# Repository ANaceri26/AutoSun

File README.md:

# AutoSun: Solar RC Car Board

One circuit board that runs a small solar-powered RC car. It charges the batteries from solar panels, swaps between two battery packs on its own, drives two rear motors and a steering servo, and holds an Arduino Nano Every as the brain.

## What the board does
- **Solar charging:** 4 small panels, wired as two pairs, charge the batteries, getting as much power from the sun as they can.
- **Two battery packs:** one drives the car while the other charges. The board switches between them automatically.
- **5 V supply:** powers the Arduino, the servo and the sensors. It stays on during a battery swap, so the Arduino never restarts.
- **Motor driver:** runs the left and right rear motors, with a built-in current limit so they can't be overloaded.
- **Plug-in spots:** steering servo, ultrasonic distance sensor, IR remote receiver, and a spare I2C port.
- **Phone control (Wi-Fi):** a spot for a XIAO ESP32-S3, with a built-in 3.3 V ↔ 5 V level shifter, so a phone can drive the car and show live battery and solar data. See `docs/phone_dashboard_plan.md`.
- **Plugs:** JST-PH 2.0 for the solar panels, both battery packs and both motors.

## Folders
| Where | What's in it |
|---|---|
| `solar_car.kicad_pro` | The KiCad 10 project. Open this to see the circuit and the board. |
| `builds/A_full_assembly/` | **Version A, ready to order:** the factory builds and solders everything except the Arduino and pin headers. Upload `gerbers_upload_this.zip`, `BOM_JLCPCB.csv` and `CPL_JLCPCB.csv`. |
| `builds/B_own_modules/` | **Version B (dropped, kept for reference only):** same board, but it uses my own red DRV8833 motor module and MP1584 5 V module instead of factory-soldered chips. Cheaper, with a bit more soldering. Same 3 files to upload. Its KiCad project is in `kicad/`. |
| `mechanical/` | For the car body: 3D models (STEP) and AutoCAD drawings (DXF), plus a sheet with every size, hole position and height. |
| `docs/` | The phone dashboard plan, and **first power-up steps** (follow these when the board arrives). |
| `sim/` | Tests: LTspice simulations (battery swap, level shifter, XIAO power) and a voltage/current stress check of the whole board. All pass. |
| `schematic_preview.png` | A quick picture of the circuit. |

The build folder has `YOU_SOLDER_THESE.csv` listing what you solder yourself: the Arduino, the XIAO and the pin headers.

## Board legend
Every plug, what goes in it, and which pin is +: see `board_legend.png` in each build folder.

## Winter charging (USB-C, no sun)
No board change needed. You make a small adapter cable instead of using the solar panels:

1. Get a **USB-C PD trigger board that outputs a fixed 12 V** (a few dollars). Fixed 12 V boards can't be set wrong. On adjustable ones, 5 V or 9 V just won't charge (simulated in `sim/charging_inputs.cir`).
2. Solder its output to a female JST-PH cable: **red to +, black to −**.
3. Unplug the solar panels from **J1** and plug the adapter in. On J1, the **left pin is +**.
4. Plug a USB-C power bank or wall charger into the trigger board. It must support USB-C PD at **12 V** (look for "12V" in its output specs; some only do 5 V and 9 V).
5. **Switch the car ON** with the main switch. The Arduino decides which pack charges, so nothing charges while it's off.

The charger then runs at its full rate (about 1 A), so a drained pack fills in about 2–3 hours. If + and − are swapped by mistake, the input diode blocks it: nothing breaks, it just won't charge.

## Open it
Install [KiCad 10](https://www.kicad.org/), then open `solar_car.kicad_pro`. In the board view, press `Alt+3` for 3D.

## Status
The board is fully laid out, passes KiCad's design checks, and every part has a JLCPCB part number. **Not ordered yet.**

Next up: write the Arduino code (driving, battery swap, IR remote, and self-driving with the ultrasonic sensor).

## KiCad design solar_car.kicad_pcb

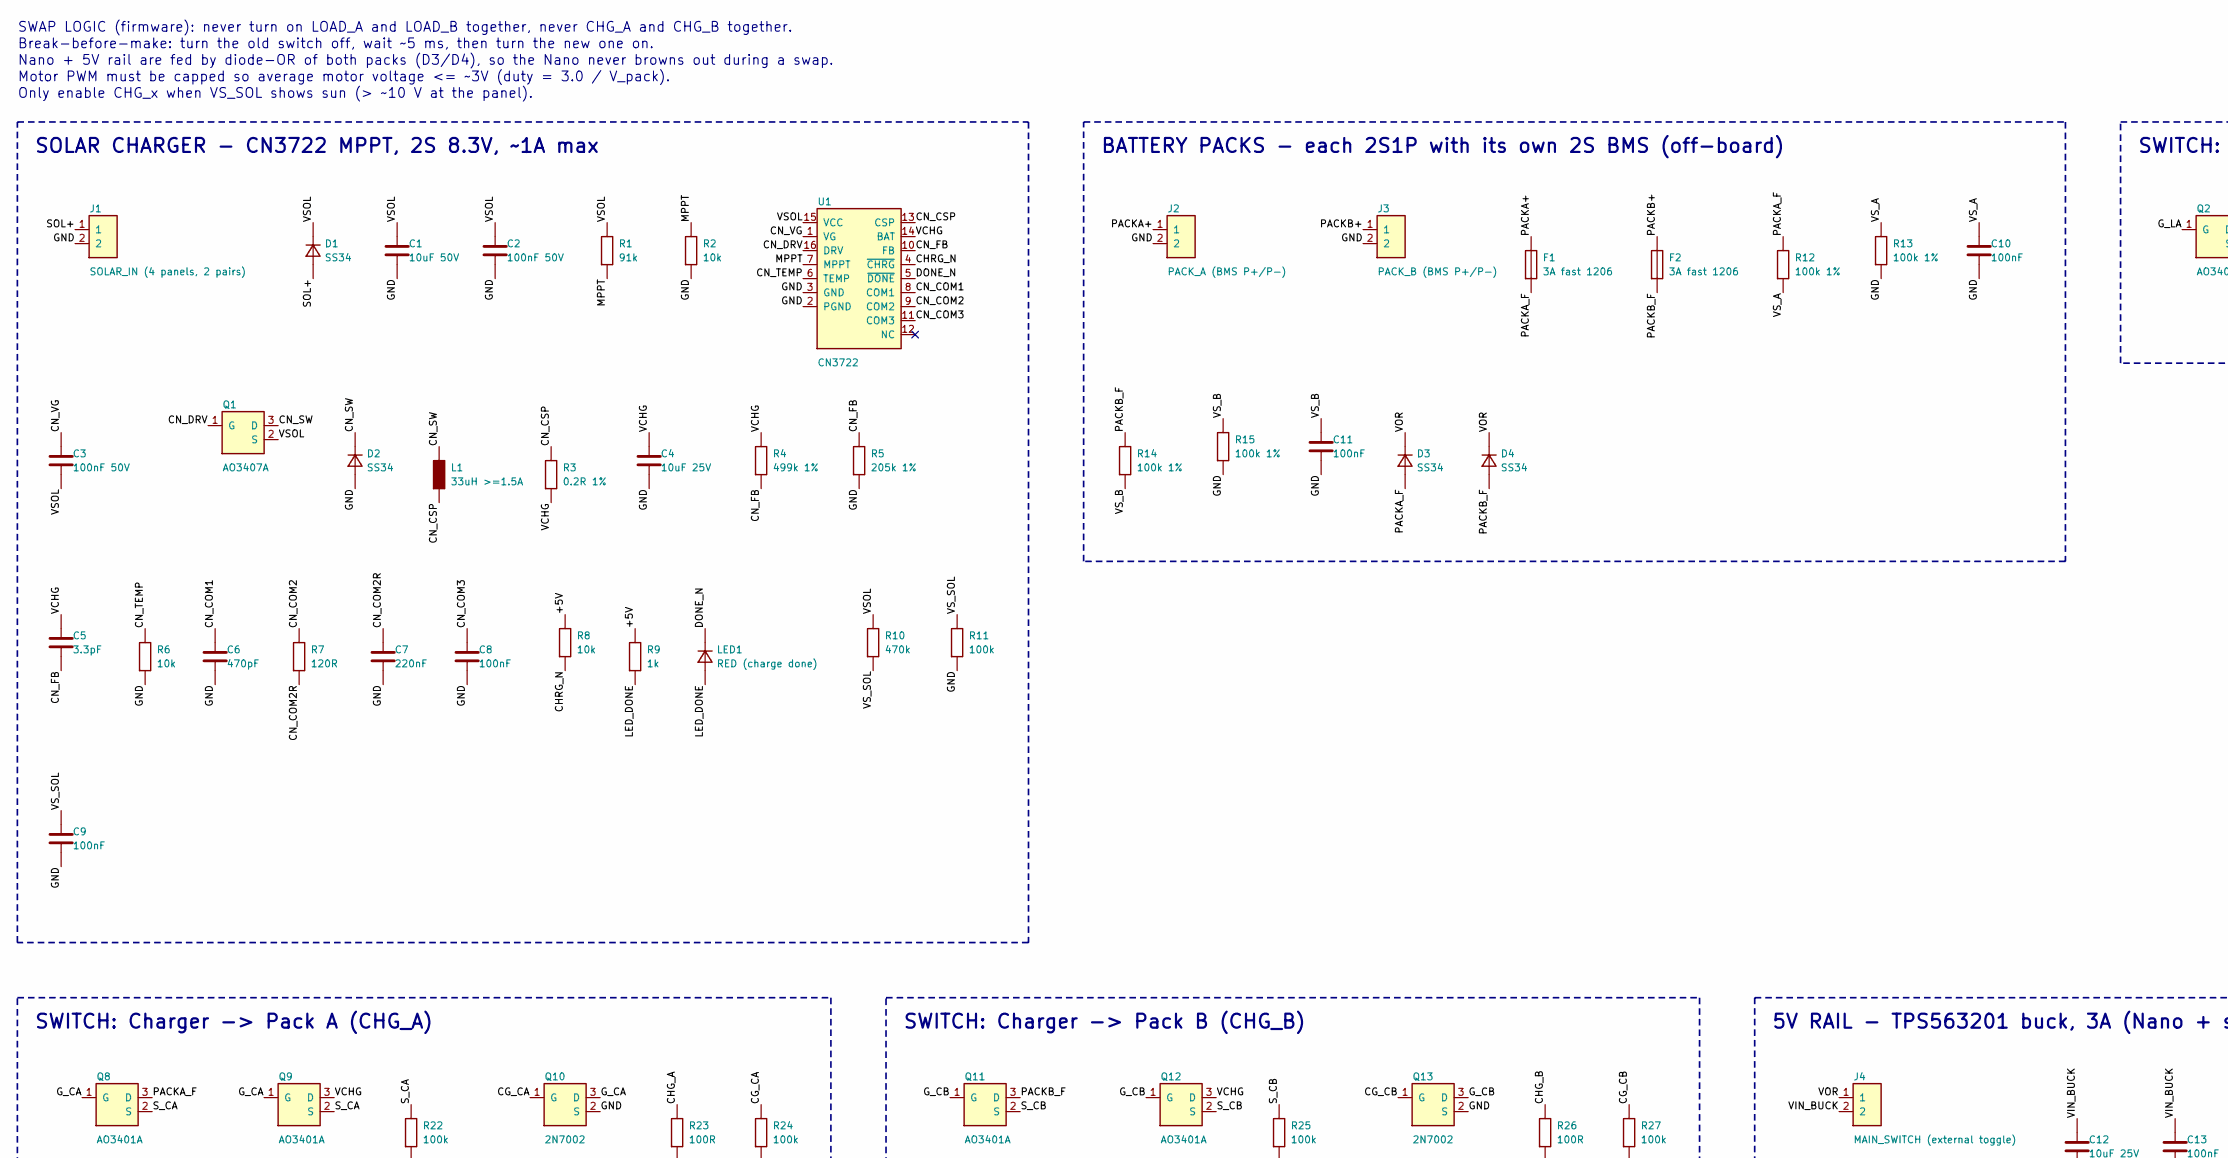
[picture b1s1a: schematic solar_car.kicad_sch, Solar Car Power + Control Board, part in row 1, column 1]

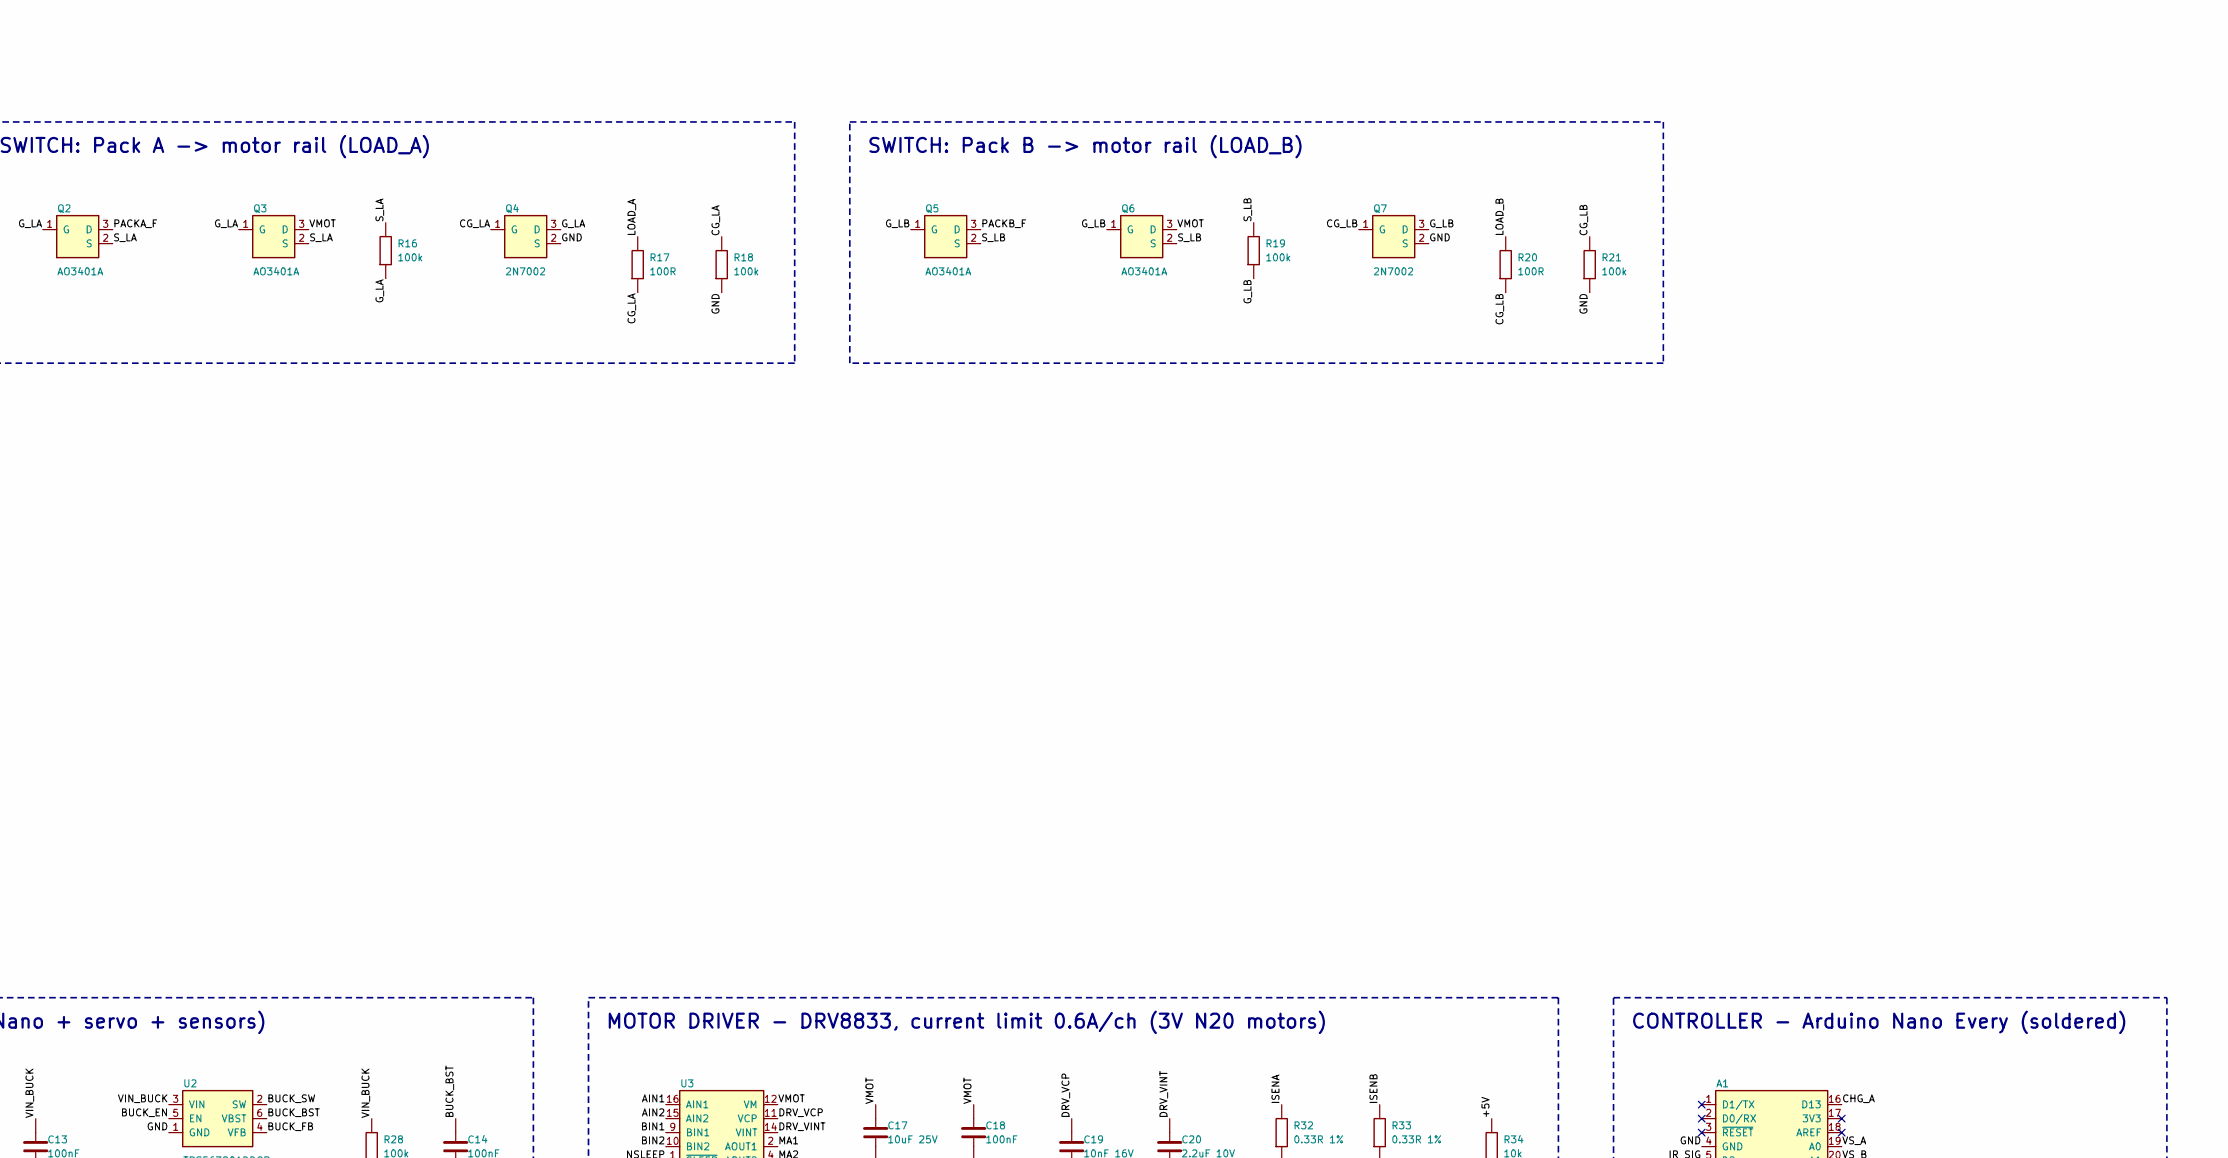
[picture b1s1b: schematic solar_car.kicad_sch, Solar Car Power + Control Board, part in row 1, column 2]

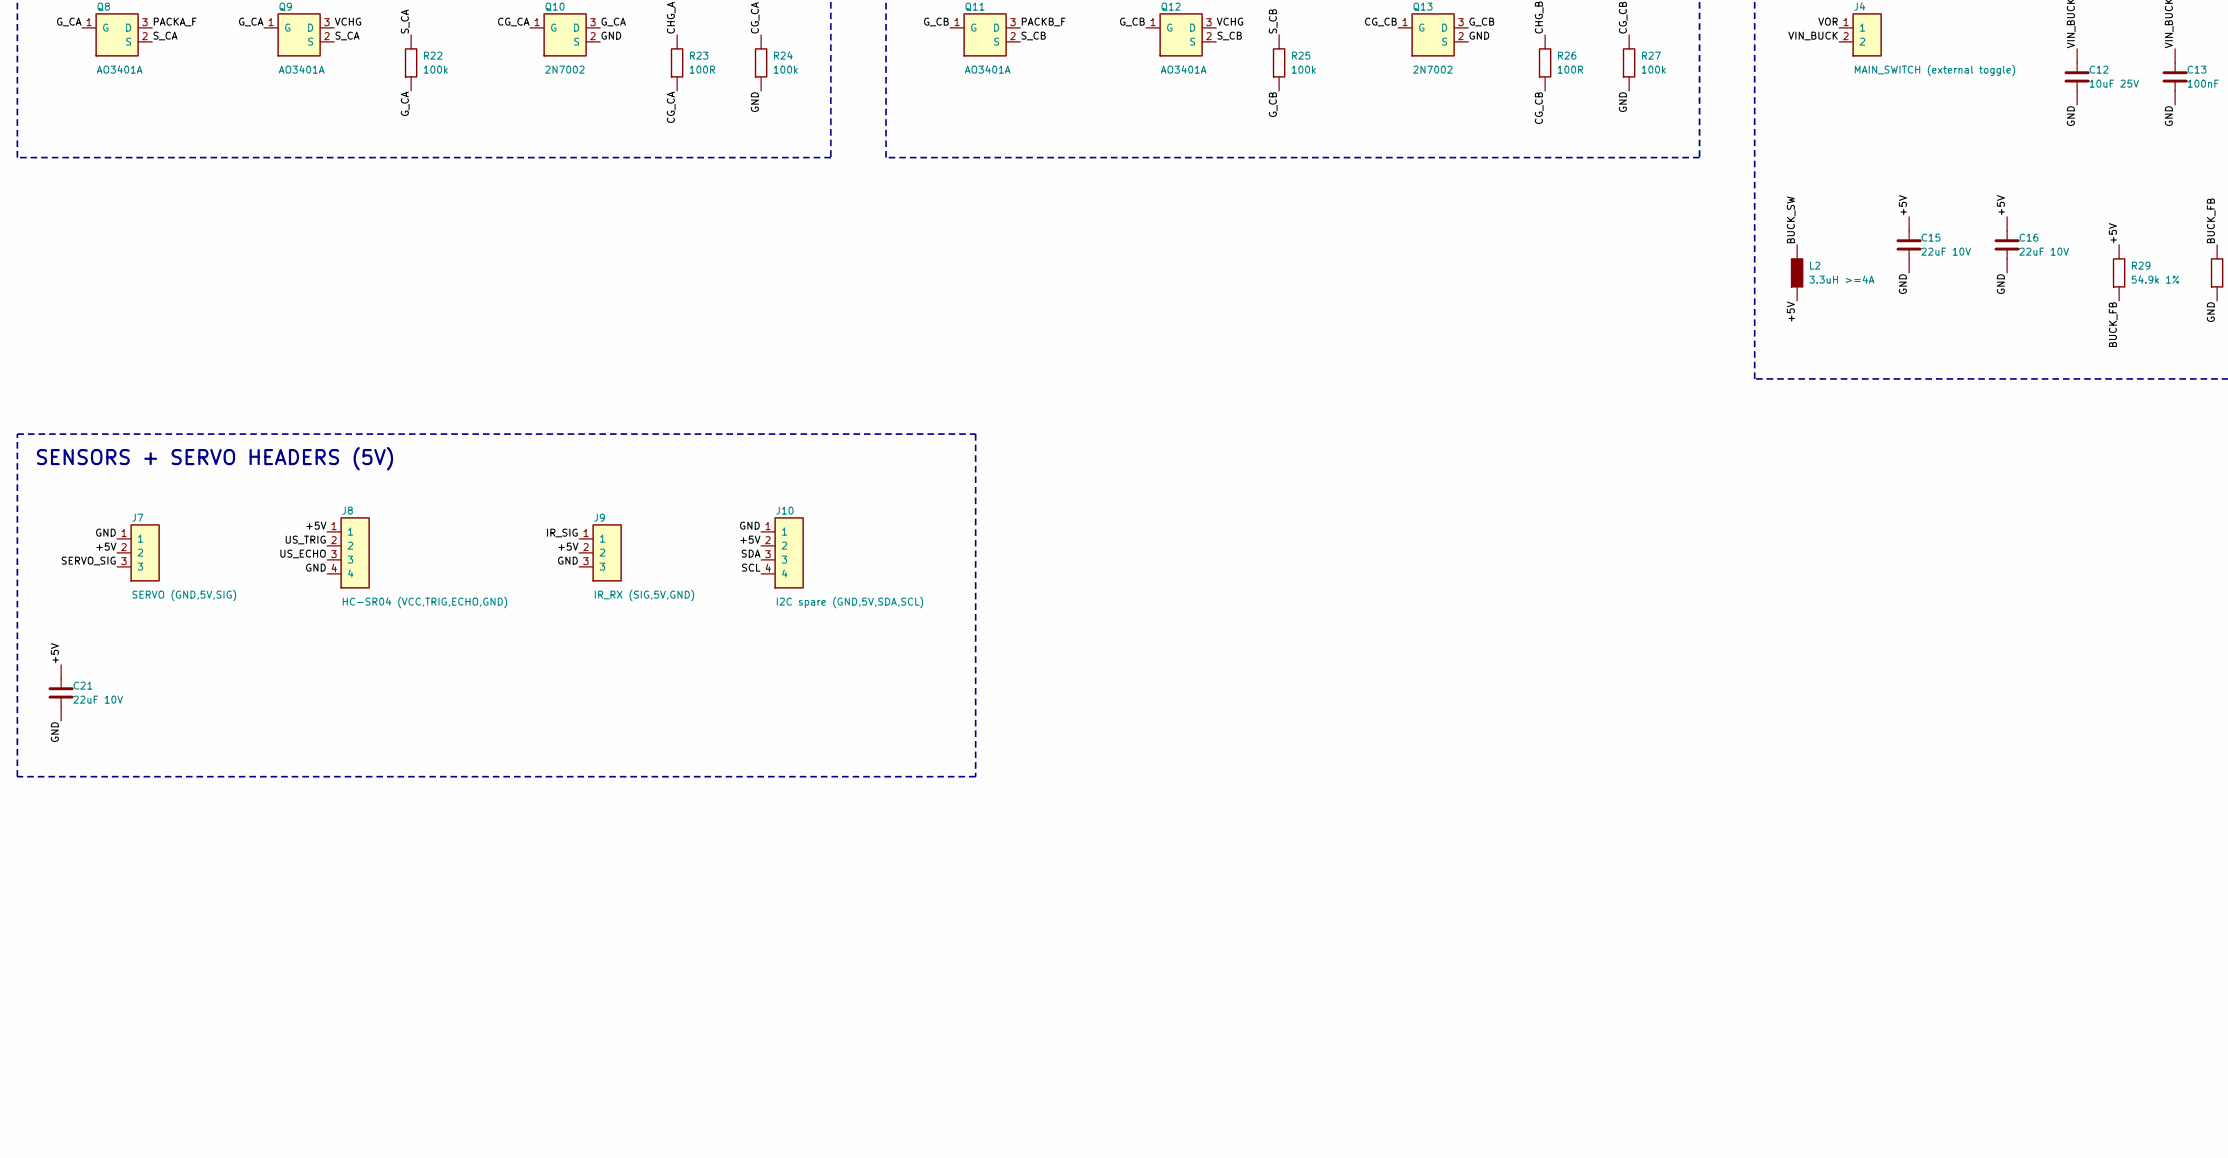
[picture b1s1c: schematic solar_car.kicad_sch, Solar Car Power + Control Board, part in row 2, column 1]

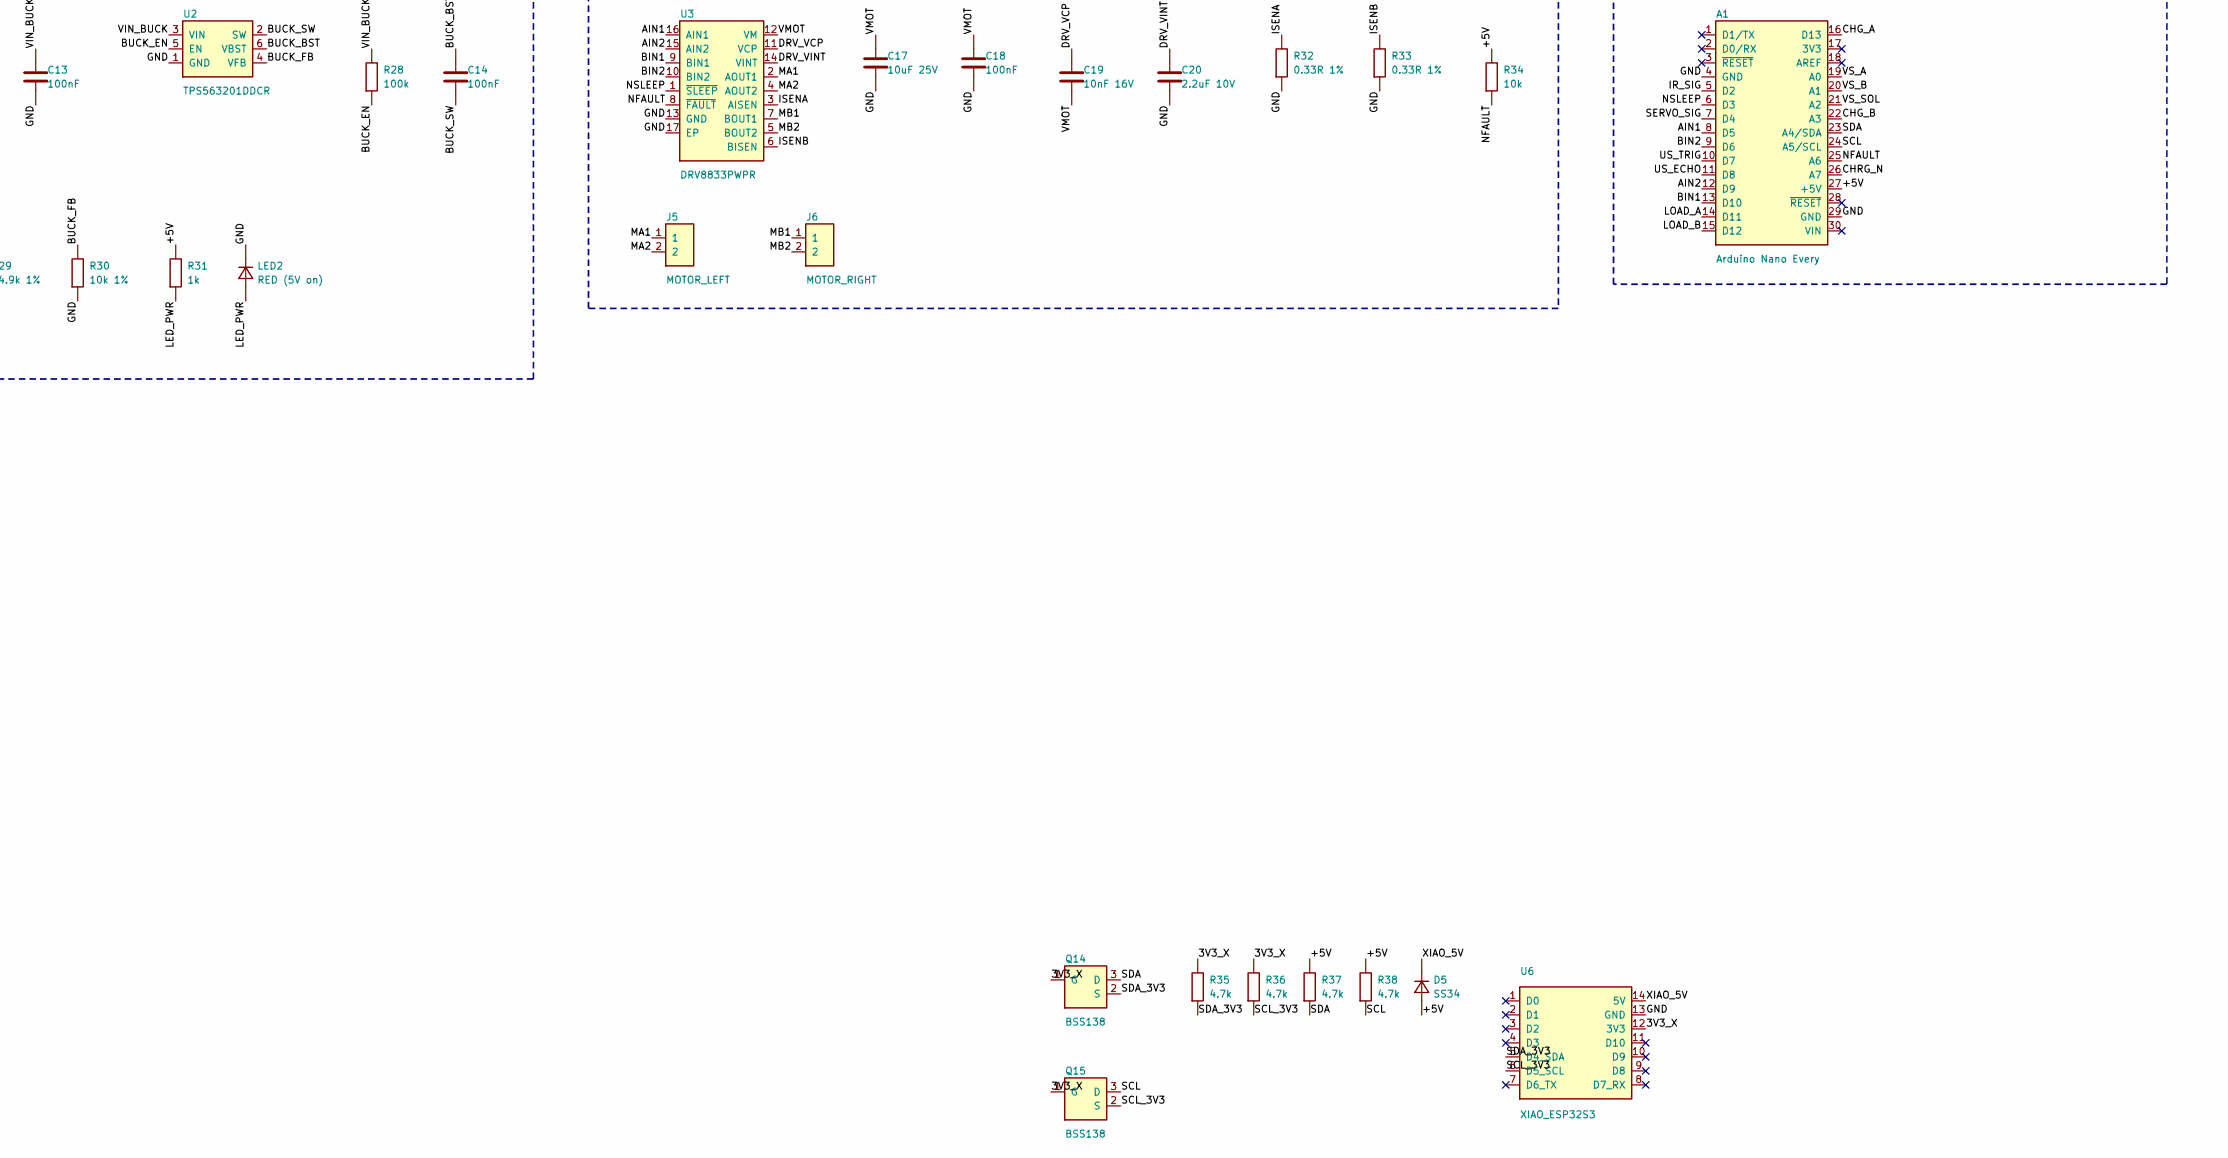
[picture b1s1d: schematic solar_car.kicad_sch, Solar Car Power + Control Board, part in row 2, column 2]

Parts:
A1: Arduino Nano Every; Arduino_Nano; MPN ABX00028
C1: 10uF 50V; C_1206_3216Metric; LCSC C13585
C2, C3: 100nF 50V; C_0603_1608Metric; LCSC C14663
C4, C12, C17: 10uF 25V; C_1206_3216Metric; LCSC C13585
C5: 3.3pF; C_0603_1608Metric; LCSC C1660
C6: 470pF; C_0603_1608Metric; LCSC C1620
C7: 220nF; C_0603_1608Metric; LCSC C21120
C8, C9, C10, C11, C13, C14, C18: 100nF; C_0603_1608Metric; LCSC C14663
C15, C16, C21: 22uF 10V; C_1206_3216Metric; LCSC C12891
C19: 10nF 16V; C_0603_1608Metric; LCSC C57112
C20: 2.2uF 10V; C_0603_1608Metric; LCSC C23630
D1, D2, D3, D4, D5: SS34; D_SMA; MPN SS34; LCSC C8678
F1, F2: 3A fast 1206; Fuse_1206_3216Metric; LCSC C14165
J1: SOLAR_IN (4 panels, 2 pairs); JST_PH_B2B-PH-K_1x02_P2.00mm_Vertical; MPN B2B-PH-K-S(LF)(SN); LCSC C131337
J2: PACK_A (BMS P+/P-); JST_PH_B2B-PH-K_1x02_P2.00mm_Vertical; MPN B2B-PH-K-S(LF)(SN); LCSC C131337
J3: PACK_B (BMS P+/P-); JST_PH_B2B-PH-K_1x02_P2.00mm_Vertical; MPN B2B-PH-K-S(LF)(SN); LCSC C131337
J4: MAIN_SWITCH (external toggle); PinHeader_1x02_P2.54mm_Vertical
J5: MOTOR_LEFT; JST_PH_B2B-PH-K_1x02_P2.00mm_Vertical; MPN B2B-PH-K-S(LF)(SN); LCSC C131337
J6: MOTOR_RIGHT; JST_PH_B2B-PH-K_1x02_P2.00mm_Vertical; MPN B2B-PH-K-S(LF)(SN); LCSC C131337
J7: SERVO (GND,5V,SIG); PinHeader_1x03_P2.54mm_Vertical
J8: HC-SR04 (VCC,TRIG,ECHO,GND); PinHeader_1x04_P2.54mm_Vertical
J9: IR_RX (SIG,5V,GND); PinHeader_1x03_P2.54mm_Vertical
J10: I2C spare (GND,5V,SDA,SCL); PinHeader_1x04_P2.54mm_Vertical
L1: 33uH >=1.5A; L_Bourns_SRN8040TA; MPN SRN8040-330M; LCSC C780189
L2: 3.3uH >=4A; L_Bourns_SRN6045TA; MPN SRN6045TA-3R3Y; LCSC C3221229
LED1: RED (charge done); LED_0603_1608Metric; LCSC C2286
LED2: RED (5V on); LED_0603_1608Metric; LCSC C2286
Q1: AO3407A; SOT-23; MPN AO3407A; LCSC C347478
Q2, Q3, Q5, Q6, Q8, Q9, Q11, Q12: AO3401A; SOT-23; MPN AO3401A; LCSC C15127
Q4, Q7, Q10, Q13: 2N7002; SOT-23; MPN 2N7002; LCSC C8545
Q14, Q15: BSS138; SOT-23; MPN BSS138LT1G; LCSC C82045
R1: 91k; R_0603_1608Metric; LCSC C23265
R2, R6, R8, R34: 10k; R_0603_1608Metric; LCSC C25804
R3: 0.2R 1%; R_1206_3216Metric; LCSC C25335
R4: 499k 1%; R_0603_1608Metric; LCSC C131054
R5: 205k 1%; R_0603_1608Metric; LCSC C5126104
R7: 120R; R_0603_1608Metric; LCSC C22787
R9, R31: 1k; R_0603_1608Metric; LCSC C21190
R10: 470k; R_0603_1608Metric; LCSC C23178
R11, R16, R18, R19, R21, R22, R24, R25, R27, R28: 100k; R_0603_1608Metric; LCSC C25803
R12, R13, R14, R15: 100k 1%; R_0603_1608Metric; LCSC C25803
R17, R20, R23, R26: 100R; R_0603_1608Metric; LCSC C22775
R29: 54.9k 1%; R_0603_1608Metric; LCSC C23077
R30: 10k 1%; R_0603_1608Metric; LCSC C25804
R32, R33: 0.33R 1%; R_1206_3216Metric; LCSC C25337
R35, R36, R37, R38: 4.7k; R_0603_1608Metric; LCSC C23162
U1: CN3722; TSSOP-16_4.4x5mm_P0.65mm; MPN CN3722; LCSC C77905
U2: TPS563201DDCR; SOT-23-6; MPN TPS563201DDCR; LCSC C116592
U3: DRV8833PWPR; HTSSOP-16-1EP_4.4x5mm_P0.65mm_EP3.4x5mm_Mask2.46x2.31mm; MPN DRV8833PWPR; LCSC C50506
U6: XIAO_ESP32S3; XIAO_ESP32S3_THT; MPN XIAO ESP32S3

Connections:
/3V3_X: Q14.1 (G), Q15.1 (G), R35.1, R36.1, U6.12 (3V3)
/+5V: A1.27 (+5V), C15.1, C16.1, C21.1, D5.2, J7.2, J8.1, J9.2, J10.2, L2.2, R8.1, R9.1, R29.1, R31.1, R34.1, R37.1, R38.1
/AIN1: A1.8 (D5), U3.16 (AIN1)
/AIN2: A1.12 (D9), U3.15 (AIN2)
/BIN1: A1.13 (D10), U3.9 (BIN1)
/BIN2: A1.9 (D6), U3.10 (BIN2)
/BUCK_BST: C14.1, U2.6 (VBST)
/BUCK_EN: R28.2, U2.5 (EN)
/BUCK_FB: R29.2, R30.1, U2.4 (VFB)
/BUCK_SW: C14.2, L2.1, U2.2 (SW)
/CG_CA: Q10.1 (G), R23.2, R24.1
/CG_CB: Q13.1 (G), R26.2, R27.1
/CG_LA: Q4.1 (G), R17.2, R18.1
/CG_LB: Q7.1 (G), R20.2, R21.1
/CHG_A: A1.16 (D13), R23.1
/CHG_B: A1.22 (A3), R26.1
/CHRG_N: A1.26 (A7), R8.2, U1.4 (~CHRG)
/CN_COM1: C6.1, U1.8 (COM1)
/CN_COM2: R7.1, U1.9 (COM2)
/CN_COM2R: C7.1, R7.2
/CN_COM3: C8.1, U1.11 (COM3)
/CN_CSP: L1.2, R3.1, U1.13 (CSP)
/CN_DRV: Q1.1 (G), U1.16 (DRV)
/CN_FB: C5.2, R4.2, R5.1, U1.10 (FB)
/CN_SW: D2.1, L1.1, Q1.3 (D)
/CN_TEMP: R6.1, U1.6 (TEMP)
/CN_VG: C3.1, U1.1 (VG)
/DONE_N: LED1.1, U1.5 (~DONE)
/DRV_VCP: C19.1, U3.11 (VCP)
/DRV_VINT: C20.1, U3.14 (VINT)
/GND: A1.4 (GND), A1.29 (GND), C1.2, C2.2, C4.2, C6.2, C7.2, C8.2, C9.2, C10.2, C11.2, C12.2, C13.2, C15.2, C16.2, C17.2, C18.2, C20.2, C21.2, D2.2, J1.2, J2.2, J3.2, J7.1, J8.4, J9.3, J10.1, LED2.1, Q4.2 (S), Q7.2 (S), Q10.2 (S), Q13.2 (S), R2.2, R5.2, R6.2, R11.2, R13.2, R15.2, R18.2, R21.2, R24.2, R27.2, R30.2, R32.2, R33.2, U1.2 (PGND), U1.3 (GND), U2.1 (GND), U3.13 (GND), U3.17 (EP), U6.13 (GND)
/G_CA: Q8.1 (G), Q9.1 (G), Q10.3 (D), R22.2
/G_CB: Q11.1 (G), Q12.1 (G), Q13.3 (D), R25.2
/G_LA: Q2.1 (G), Q3.1 (G), Q4.3 (D), R16.2
/G_LB: Q5.1 (G), Q6.1 (G), Q7.3 (D), R19.2
/IR_SIG: A1.5 (D2), J9.1
/ISENA: R32.1, U3.3 (AISEN)
/ISENB: R33.1, U3.6 (BISEN)
/LED_DONE: LED1.2, R9.2
/LED_PWR: LED2.2, R31.2
/LOAD_A: A1.14 (D11), R17.1
/LOAD_B: A1.15 (D12), R20.1
/MA1: J5.1, U3.2 (AOUT1)
/MA2: J5.2, U3.4 (AOUT2)
/MB1: J6.1, U3.7 (BOUT1)
/MB2: J6.2, U3.5 (BOUT2)
/MPPT: R1.2, R2.1, U1.7 (MPPT)
/NFAULT: A1.25 (A6), R34.2, U3.8 (~FAULT)
/NSLEEP: A1.6 (D3), U3.1 (~SLEEP)
/PACKA+: F1.1, J2.1
/PACKA_F: D3.2, F1.2, Q2.3 (D), Q8.3 (D), R12.1
/PACKB+: F2.1, J3.1
/PACKB_F: D4.2, F2.2, Q5.3 (D), Q11.3 (D), R14.1
/SCL: A1.24 (A5/SCL), J10.4, Q15.3 (D), R38.2
/SCL_3V3: Q15.2 (S), R36.2, U6.6 (D5_SCL)
/SDA: A1.23 (A4/SDA), J10.3, Q14.3 (D), R37.2
/SDA_3V3: Q14.2 (S), R35.2, U6.5 (D4_SDA)
/SERVO_SIG: A1.7 (D4), J7.3
/SOL+: D1.2, J1.1
/S_CA: Q8.2 (S), Q9.2 (S), R22.1
/S_CB: Q11.2 (S), Q12.2 (S), R25.1
/S_LA: Q2.2 (S), Q3.2 (S), R16.1
/S_LB: Q5.2 (S), Q6.2 (S), R19.1
/US_ECHO: A1.11 (D8), J8.3
/US_TRIG: A1.10 (D7), J8.2
/VCHG: C4.1, C5.1, Q9.3 (D), Q12.3 (D), R3.2, R4.1, U1.14 (BAT)
/VIN_BUCK: C12.1, C13.1, J4.2, R28.1, U2.3 (VIN)
/VMOT: C17.1, C18.1, C19.2, Q3.3 (D), Q6.3 (D), U3.12 (VM)
/VOR: D3.1, D4.1, J4.1
/VSOL: C1.1, C2.1, C3.2, D1.1, Q1.2 (S), R1.1, R10.1, U1.15 (VCC)
/VS_A: A1.19 (A0), C10.1, R12.2, R13.1
/VS_B: A1.20 (A1), C11.1, R14.2, R15.1
/VS_SOL: A1.21 (A2), C9.1, R10.2, R11.1
/XIAO_5V: D5.1, U6.14 (5V)

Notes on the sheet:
SOLAR CHARGER - CN3722 MPPT, 2S 8.3V, ~1A max
SWITCH: Pack A -> motor rail (LOAD_A)
Motor PWM must be capped so average motor voltage <= ~3V (duty = 3.0 / V_pack).
BATTERY PACKS - each 2S1P with its own 2S BMS (off-board)
MOTOR DRIVER - DRV8833, current limit 0.6A/ch (3V N20 motors)
Nano + 5V rail are fed by diode-OR of both packs (D3/D4), so the Nano never browns out during a swap.
SWAP LOGIC (firmware): never turn on LOAD_A and LOAD_B together, never CHG_A and CHG_B together.
SWITCH: Charger -> Pack A (CHG_A)
Only enable CHG_x when VS_SOL shows sun (> ~10 V at the panel).
Break-before-make: turn the old switch off, wait ~5 ms, then turn the new one on.
SENSORS + SERVO HEADERS (5V)
SWITCH: Pack B -> motor rail (LOAD_B)
SWITCH: Charger -> Pack B (CHG_B)
5V RAIL - TPS563201 buck, 3A (Nano + servo + sensors)
CONTROLLER - Arduino Nano Every (soldered)

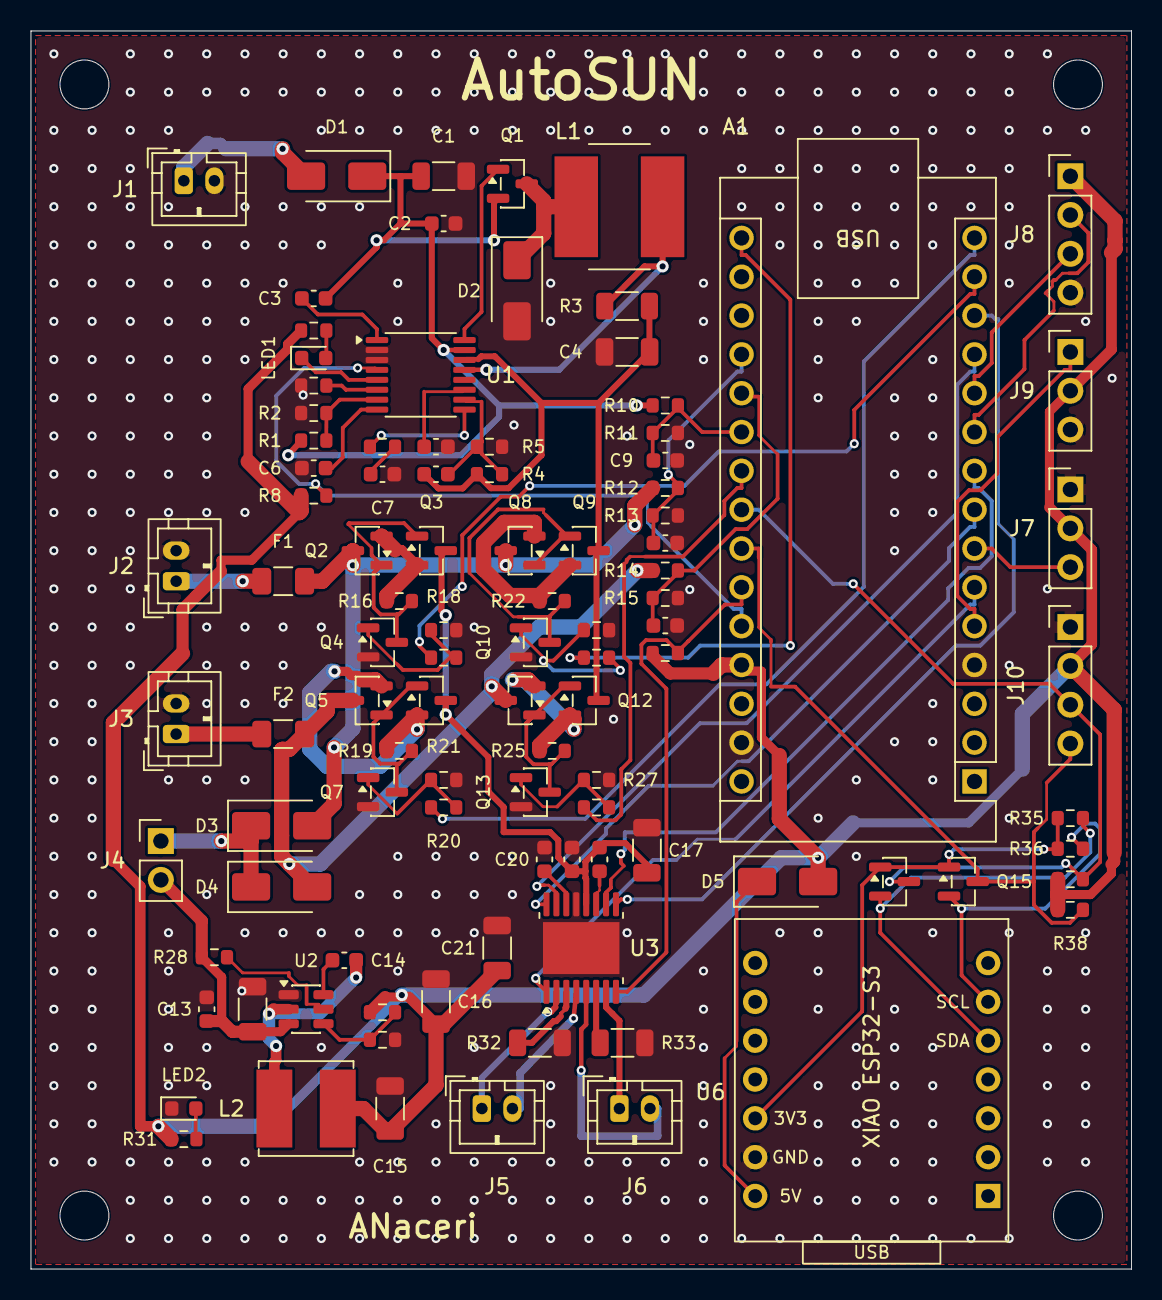
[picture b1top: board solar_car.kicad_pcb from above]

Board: 2 copper layers, 72.0 x 81.0 mm, 104 parts (0 on the bottom side), 74 nets.

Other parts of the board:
H1, H2, H3, H4: MountingHole_3.2mm_M3

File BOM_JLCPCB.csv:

Comment,Designator,Footprint,MPN,LCSC Part #
SOLAR_IN (3 panels in series),J1,JST_XH_B2B-XH-A_1x02_P2.50mm_Vertical,,
SS34,"D1,D2,D3,D4",D_SMA,SS34,
10uF 50V,C1,C_1206_3216Metric,,
100nF 50V,"C2,C3",C_0603_1608Metric,,
150k,R1,R_0603_1608Metric,,
10k,"R2,R6,R8,R34",R_0603_1608Metric,,
CN3722,U1,TSSOP-16_4.4x5mm_P0.65mm,CN3722,C77905
AO3407A,Q1,SOT-23,AO3407A,
22uH >=1.5A,L1,L_Bourns_SRN8040TA,SRN8040TA-220M,
0.2R 1%,R3,R_1206_3216Metric,,
10uF 25V,"C4,C12,C17",C_1206_3216Metric,,
499k 1%,R4,R_0603_1608Metric,,
205k 1%,R5,R_0603_1608Metric,,
3.3pF,C5,C_0603_1608Metric,,
470pF,C6,C_0603_1608Metric,,
120R,R7,R_0603_1608Metric,,
220nF,C7,C_0603_1608Metric,,
100nF,"C8,C9,C10,C11,C13,C14,C18",C_0603_1608Metric,,
1k,"R9,R31",R_0603_1608Metric,,
GREEN (charge done),LED1,LED_0603_1608Metric,,
470k,R10,R_0603_1608Metric,,
100k,"R11,R16,R18,R19,R21,R22,R24,R25,R27,R28",R_0603_1608Metric,,
PACK_A (BMS P+/P-),J2,JST_XH_B2B-XH-A_1x02_P2.50mm_Vertical,,
PACK_B (BMS P+/P-),J3,JST_XH_B2B-XH-A_1x02_P2.50mm_Vertical,,
3A fast 1206,"F1,F2",Fuse_1206_3216Metric,,
100k 1%,"R12,R13,R14,R15",R_0603_1608Metric,,
AO3401A,"Q2,Q3,Q5,Q6,Q8,Q9,Q11,Q12",SOT-23,AO3401A,
2N7002,"Q4,Q7,Q10,Q13",SOT-23,2N7002,
100R,"R17,R20,R23,R26",R_0603_1608Metric,,
TPS563201DDCR,U2,SOT-23-6,TPS563201DDCR,
3.3uH >=4A,L2,L_Bourns_SRN6045TA,SRN6045TA-3R3Y,
22uF 10V,"C15,C16,C21",C_1206_3216Metric,,
54.9k 1%,R29,R_0603_1608Metric,,
10k 1%,R30,R_0603_1608Metric,,
RED (5V on),LED2,LED_0603_1608Metric,,
DRV8833PWPR,U3,HTSSOP-16-1EP_4.4x5mm_P0.65mm_EP3.4x5mm_Mask2.46x2.31mm,DRV8833PWPR,
10nF 16V,C19,C_0603_1608Metric,,
2.2uF 10V,C20,C_0603_1608Metric,,
0.33R 1%,"R32,R33",R_1206_3216Metric,,
MOTOR_LEFT,J5,JST_XH_B2B-XH-A_1x02_P2.50mm_Vertical,,
MOTOR_RIGHT,J6,JST_XH_B2B-XH-A_1x02_P2.50mm_Vertical,,

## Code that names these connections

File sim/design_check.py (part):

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# worst-case net voltages (V): solar = 2 pairs Voc ~14 V; mis-wired 4-in-series would be ~28 V (still checked)
VMAX={'GATE8':8.0,'SOL+':15.0,'VSOL':15.0,'MISWIRE':28.0,'VCHG':9.0,'PACK':8.4,'VMOT':8.4,'VOR':8.4,'+5V':5.1,'XIAO_5V':4.8,'3V3':3.3,'LOGIC5':5.1,'ADC_PACK':4.2,'ADC_SOL':2.63}
checks=[ # part, what, net, rating
 ('U1 CN3722','VCC pin','VSOL',30.0),('U1 CN3722','BAT/CSP pins','VCHG',28.0),('U1 CN3722','CHRG/DONE pins','LOGIC5',30.0),
 ('Q1 AO3407A','drain-source','VSOL',30.0),('Q1 AO3407A','gate (charger clamps it to 8 V)','GATE8',20.0),
 ('D1/D2 SS34','reverse voltage','VSOL',40.0),('D3/D4 SS34','reverse voltage','PACK',40.0),
 ('Q2-Q12 AO3401A','drain-source','PACK',30.0),('Q2-Q12 AO3401A','gate-source (= pack or charger V)','VCHG',12.0),
 ('Q4-Q13 2N7002','drain-source','PACK',60.0),('Q4-Q13 2N7002','gate (Arduino pin)','LOGIC5',20.0),
 ('U2 TPS563201','VIN','VOR',17.0),('U3 DRV8833','VM','VMOT',11.8),('U3 DRV8833','logic inputs','LOGIC5',7.0),
 ('A1 Nano Every','5V pin (regulated 5.0 V)','+5V',6.0),('A1 Nano Every','A0/A1 pin (full pack x0.5; reads up to 5.0 V, damage above 5.5 V)','ADC_PACK',5.5),('A1 Nano Every','A2 pin (solar x0.175)','ADC_SOL',5.0),
 ('U6 XIAO','5V pin (after D5)','XIAO_5V',5.5),('U6 XIAO','SDA/SCL (pulled to its own 3.3 V)','3V3',3.6),
 ('Q14/Q15 BSS138','drain-source','LOGIC5',50.0),('Q14/Q15 BSS138','gate-source','3V3',20.0),
 ('C1/C2/C3 (50 V)','capacitor','VSOL',50.0),('C4/C5 (50 V)','capacitor','VCHG',50.0),('C12/C13 (50 V)','capacitor','VOR',50.0),
 ('C15/C16/C21 (25 V)','capacitor','+5V',25.0),('C17/C18 (50 V)','capacitor','VMOT',50.0),
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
